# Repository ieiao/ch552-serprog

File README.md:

# ch552-serprog

# 简介

使用ch552设计的兼容[flashrom](https://flashrom.org) serprog协议的SPI nor flash烧录器，支持3.3V和1.8V电压。

# 固件

本仓库仅包含原理图及PCB文件，程序在[这个仓库](https://github.com/ieiao/ch554_sdcc)的`serprog`分支`examples/serprog`目录下。

# 使用方法

```shell
$ # 读flash
$ flashrom -p serprog:dev=/dev/ttyACM0:4000000 -r /tmp/read.bin
$ # 擦除flash
$ flashrom -p serprog:dev=/dev/ttyACM0:4000000 -E
$ # 写flash
$ flashrom -p serprog:dev=/dev/ttyACM0:4000000 -w /tmp/read.bin
```

受ch552性能以及程序实现影响，flash读写速度未能达到上限，以下是使用SST25VF032B 32Mbit(4Mbyte) flash测出的读写平均耗时

| 操作 | 耗时 |
| :--: | :--: |
| 全片读 | 10s |
| 全片擦除 | 30s |
| 全片读+写+校验 | 32s |

# 备注

* 原理图中的led灯需要二选一焊接，不可全部焊接
* 如果使用TXS0104，flash测上拉电阻可以不焊接

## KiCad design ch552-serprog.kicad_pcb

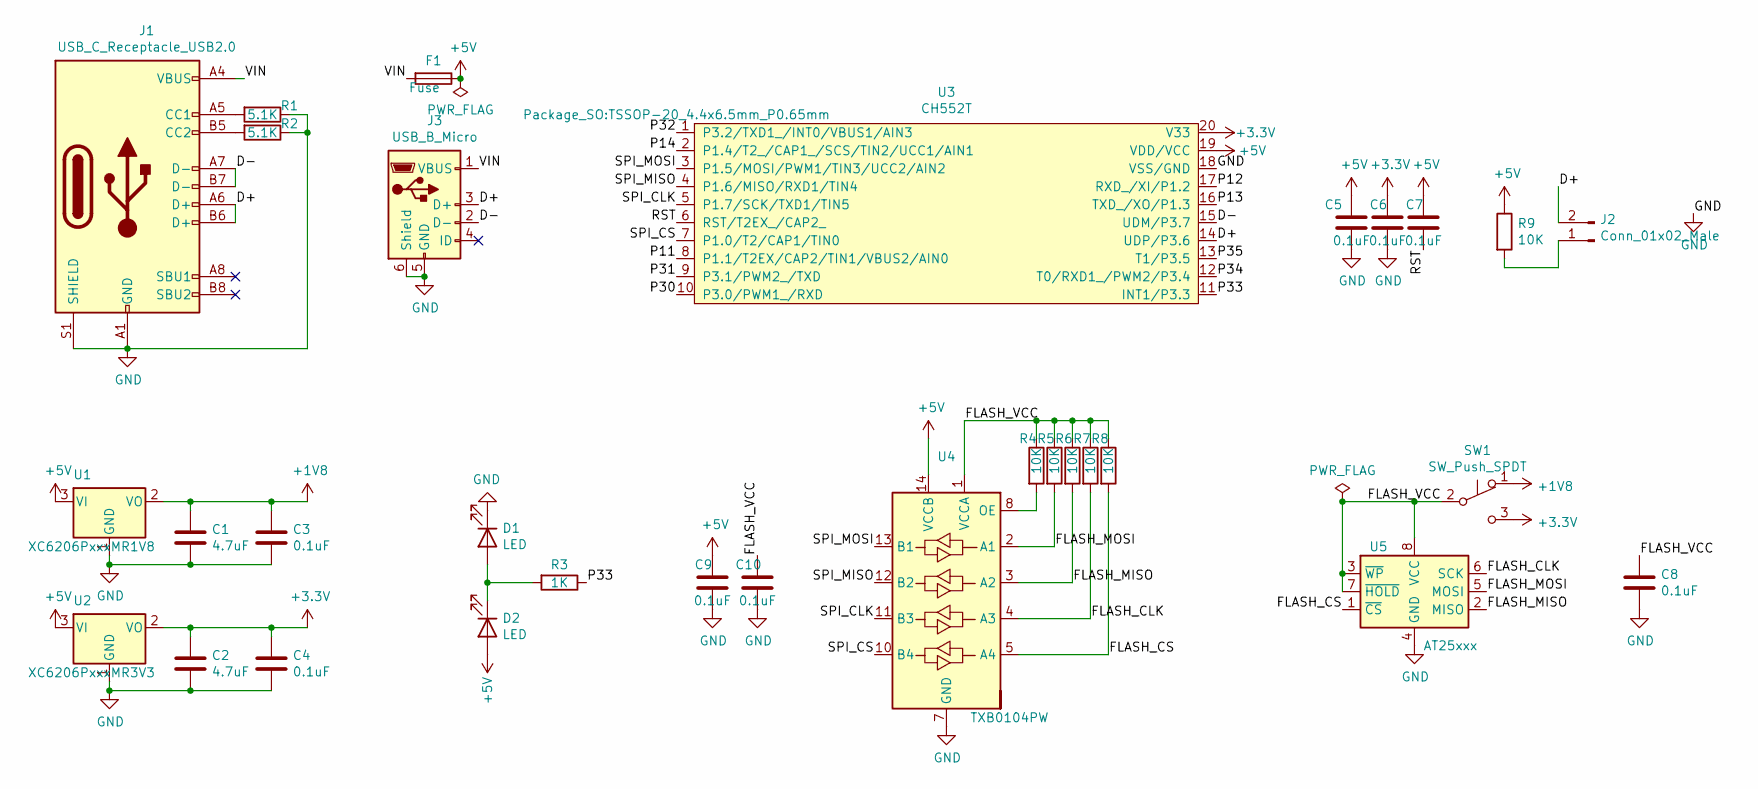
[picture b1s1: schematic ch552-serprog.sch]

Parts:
C1, C2: 4.7uF; C_0603_1608Metric
C3, C4, C5, C6, C7, C8, C9, C10: 0.1uF; C_0603_1608Metric
D1, D2: LED; LED_0603_1608Metric
F1: Fuse; Fuse_1210_3225Metric
J1: USB_C_Receptacle_USB2.0; USB_C_Receptacle_Palconn_UTC16-G
J2: Conn_01x02_Male; PinHeader_1x02_P2.00mm_Vertical
J3: USB_B_Micro; USB_Micro-B_Molex-105017-0001
R1, R2: 5.1K; R_0603_1608Metric
R3: 1K; R_0603_1608Metric
R4, R5, R6, R7, R8, R9: 10K; R_0603_1608Metric
SW1: SW_Push_SPDT; SW-DIP-3
U1: XC6206PxxxMR1V8; SOT-23
U2: XC6206PxxxMR3V3; SOT-23
U3: CH552T; TSSOP-20_4.4x6.5mm_P0.65mm
U4: TXB0104PW; TSSOP-14_4.4x5mm_P0.65mm
U5: AT25xxx; DIP-8_W7.62mm

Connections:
+1V8: C1.1, C3.1, SW1.1 (A), U1.2 (VO)
+3V3: C2.1, C4.1, C6.2, SW1.3 (C), U2.2 (VO), U3.20 (V33)
+5V: C5.2, C7.2, C9.2, D2.2 (A), F1.1, R9.1, U1.3 (VI), U2.3 (VI), U3.19 (VDD/VCC), U4.14 (VCCB)
/D+: J1.A6 (D+), J1.B6 (D+), J2.2, J3.3 (D+), U3.14 (UDP/P3.6)
/D-: J1.A7 (D-), J1.B7 (D-), J3.2 (D-), U3.15 (UDM/P3.7)
/FLASH_CLK: R7.2, U4.4 (A3), U5.6 (SCK)
/FLASH_CS: R8.2, U4.5 (A4), U5.1 (~CS)
/FLASH_MISO: R6.2, U4.3 (A2), U5.2 (MISO)
/FLASH_MOSI: R5.2, U4.2 (A1), U5.5 (MOSI)
/FLASH_VCC: C8.1, C10.2, R4.1, R5.1, R6.1, R7.1, R8.1, SW1.2 (B), U4.1 (VCCA), U5.3 (~WP), U5.7 (~HOLD), U5.8 (VCC)
/P11: U3.8 (P1.1/T2EX/CAP2/TIN1/VBUS2/AIN0)
/P12: U3.17 (RXD_/XI/P1.2)
/P13: U3.16 (TXD_/XO/P1.3)
/P14: U3.2 (P1.4/T2_/CAP1_/SCS/TIN2/UCC1/AIN1)
/P30: U3.10 (P3.0/PWM1_/RXD)
/P31: U3.9 (P3.1/PWM2_/TXD)
/P32: U3.1 (P3.2/TXD1_/INT0/VBUS1/AIN3)
/P33: R3.1, U3.11 (INT1/P3.3)
/P34: U3.12 (T0/RXD1_/PWM2/P3.4)
/P35: U3.13 (T1/P3.5)
/RST: C7.1, U3.6 (RST/T2EX_/CAP2_)
/SPI_CLK: U3.5 (P1.7/SCK/TXD1/TIN5), U4.11 (B3)
/SPI_CS: U3.7 (P1.0/T2/CAP1/TIN0), U4.10 (B4)
/SPI_MISO: U3.4 (P1.6/MISO/RXD1/TIN4), U4.12 (B2)
/SPI_MOSI: U3.3 (P1.5/MOSI/PWM1/TIN3/UCC2/AIN2), U4.13 (B1)
/VIN: F1.2, J1.A4 (VBUS), J1.A9 (VBUS), J1.B4 (VBUS), J1.B9 (VBUS), J3.1 (VBUS)
GND: C1.2, C2.2, C3.2, C4.2, C5.1, C6.1, C8.2, C9.1, C10.1, D1.1 (K), J1.A1 (GND), J1.A12 (GND), J1.B1 (GND), J1.B12 (GND), J1.S1 (SHIELD), J3.5 (GND), J3.6 (Shield), R1.1, R2.1, U1.1 (GND), U2.1 (GND), U3.18 (VSS/GND), U4.7 (GND), U5.4 (GND)
unnamed: D1.2 (A), D2.1 (K), R3.2
unnamed: J1.A5 (CC1), R1.2
unnamed: J1.B5 (CC2), R2.2
unnamed: J2.1, R9.2
unnamed: R4.2, U4.8 (OE)

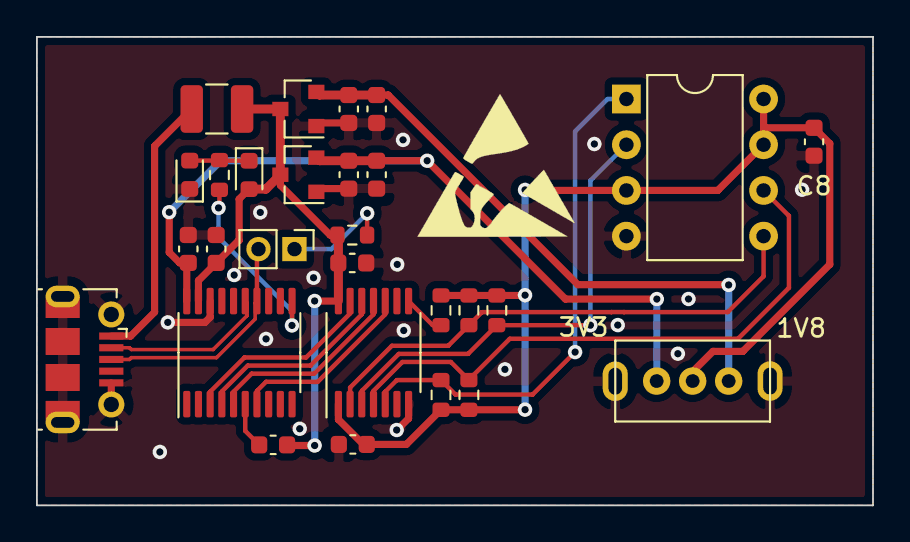
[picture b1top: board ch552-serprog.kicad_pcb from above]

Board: 2 copper layers, 46.4 x 26.0 mm, 28 parts (0 on the bottom side), 21 nets.

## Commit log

2022-01-23 add gitignore
2022-01-23 ch552-serprog: v0.1
